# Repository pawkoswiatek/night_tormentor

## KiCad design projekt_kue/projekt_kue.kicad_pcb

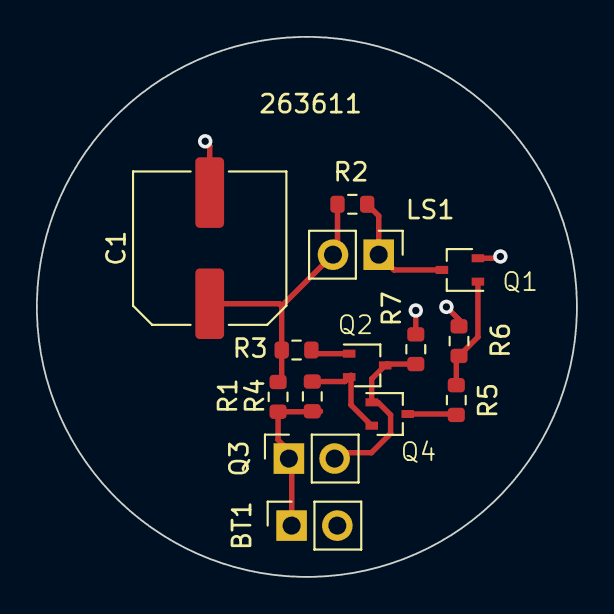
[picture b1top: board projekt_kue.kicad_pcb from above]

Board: 2 copper layers, 30.0 x 30.0 mm, 14 parts (0 on the bottom side), 9 nets.

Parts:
BT1: Battery CR2032; PinSocket_1x02_P2.54mm_Vertical
C1: 220u; C_Elec_8x6.2
LS1: Speaker_Crystal; PinHeader_1x02_P2.54mm_Vertical
Q1: NPN; jakis_tranzystor_przyklad
Q2, Q4: PNP; jakis_tranzystor_przyklad
Q3: Q_Photo_NPN; PinSocket_1x02_P2.54mm_Vertical
R1: 47k; R_0603_1608Metric
R2: 1k; R_0603_1608Metric
R3: 100k; R_0603_1608Metric
R4: 22k; R_0603_1608Metric
R5: 4.7k; R_0603_1608Metric
R6: 1meg; R_0603_1608Metric
R7: 220k; R_0603_1608Metric

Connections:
+1V5: BT1.1 (+), Q3.1 (C), R1.1, R4.1
GND: BT1.2 (-), C1.2, Q1.3 (E), R6.2, R7.2
unnamed: C1.1, LS1.2, R1.2, R2.1, R3.1
unnamed: Q1.2 (B), R5.2, R6.1
unnamed: LS1.1, Q1.1 (C), R2.2
unnamed: Q2.2 (B), R3.2
unnamed: Q2.1 (C), Q3.2 (E), Q4.2 (B), R7.1
unnamed: Q2.3 (E), Q4.3 (E), R4.2
unnamed: Q4.1 (C), R5.1
